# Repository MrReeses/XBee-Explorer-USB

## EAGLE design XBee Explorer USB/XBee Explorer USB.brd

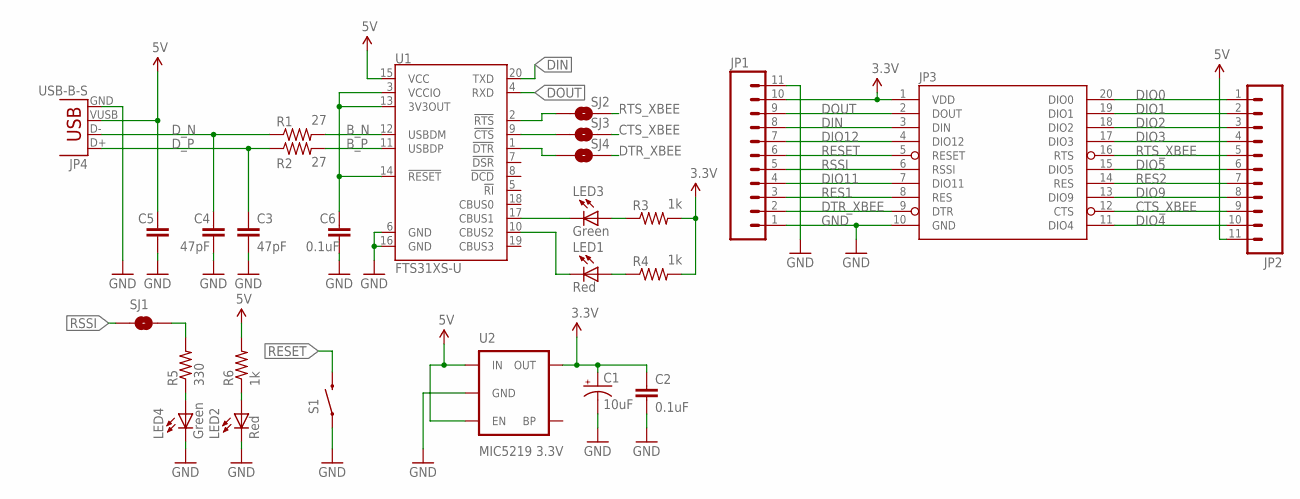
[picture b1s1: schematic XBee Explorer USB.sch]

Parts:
C1: 10uF; EIA3216
C2, C6: 0.1uF; 0805
C3, C4: 47pF; 0805
C5: CAP0805; 0805
JP1, JP2: M111X11_NO_SILK; 1X11_NO_SILK
JP3: XBEE-1B3; XBEE-SMD
JP4: USB-B-S; USB-B-SMT
LED1, LED2: Red; CHIP-LED0805
LED3, LED4: Green; CHIP-LED0805
R1, R2: 27; R0805
R3, R4, R6: 1k; R0805
R5: 330; R0805
S1: SWITCH-MOMENTARY-2SMD; TACTILE-SWITCH-SMD
SJ1, SJ2, SJ3, SJ4: SOLDERJUMPERTRACE; SJ_2S-TRACE
U1: FTS31XS-U; SSOP20_L
U2: MIC5219 3.3V; SOT23-5

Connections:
3.3V: C1.A (+), C2.1, JP1.10, JP3.1 (VDD), R3.2, R4.2, U2.5 (OUT)
5V: C5.1, JP2.11, JP4.VUSB (VBUS), R6.2, U1.15 (VCC), U2.1 (IN), U2.3 (EN)
B_N: R1.2, U1.12 (USBDM)
B_P: R2.2, U1.11 (USBDP)
CTS_XBEE: JP2.9, JP3.12 (CTS), SJ3.2
DIN: JP1.8, JP3.3 (DIN), U1.20 (TXD)
DIO0: JP2.1, JP3.20 (DIO0)
DIO1: JP2.2, JP3.19 (DIO1)
DIO2: JP2.3, JP3.18 (DIO2)
DIO3: JP2.4, JP3.17 (DIO3)
DIO4: JP2.10, JP3.11 (DIO4)
DIO5: JP2.6, JP3.15 (DIO5)
DIO9: JP2.8, JP3.13 (DIO9)
DIO11: JP1.4, JP3.7 (DIO11)
DIO12: JP1.7, JP3.4 (DIO12)
DOUT: JP1.9, JP3.2 (DOUT), U1.4 (RXD)
DTR_XBEE: JP1.2, JP3.9 (DTR), SJ4.2
D_N: C4.1, JP4.D-, R1.1
D_P: C3.1, JP4.D+, R2.1
GND: C1.C (-), C2.2, C3.2, C4.2, C5.2, C6.2, JP1.1, JP1.11, JP3.10 (GND), JP4.GND, LED2.C, LED4.C, S1.1, U1.6 (GND), U1.16 (GND), U2.2 (GND)
unnamed: SJ2.1, U1.2 (!RTS)
unnamed: SJ3.1, U1.9 (!CTS)
unnamed: SJ4.1, U1.1 (!DTR)
unnamed: R5.2, SJ1.2
unnamed: LED2.A, R6.1
unnamed: LED4.A, R5.1
unnamed: LED3.C, U1.17 (CBUS1)
unnamed: LED1.C, U1.10 (CBUS2)
unnamed: LED3.A, R3.1
unnamed: LED1.A, R4.1
unnamed: C6.1, U1.3 (VCCIO), U1.13 (3V3OUT), U1.14 (!RESET)
RES1: JP1.3, JP3.8 (RES)
RES2: JP2.7, JP3.14 (RES)
RESET: JP1.6, JP3.5 (RESET), S1.3 (2)
RSSI: JP1.5, JP3.6 (RSSI), SJ1.1
RTS_XBEE: JP2.5, JP3.16 (RTS), SJ2.2

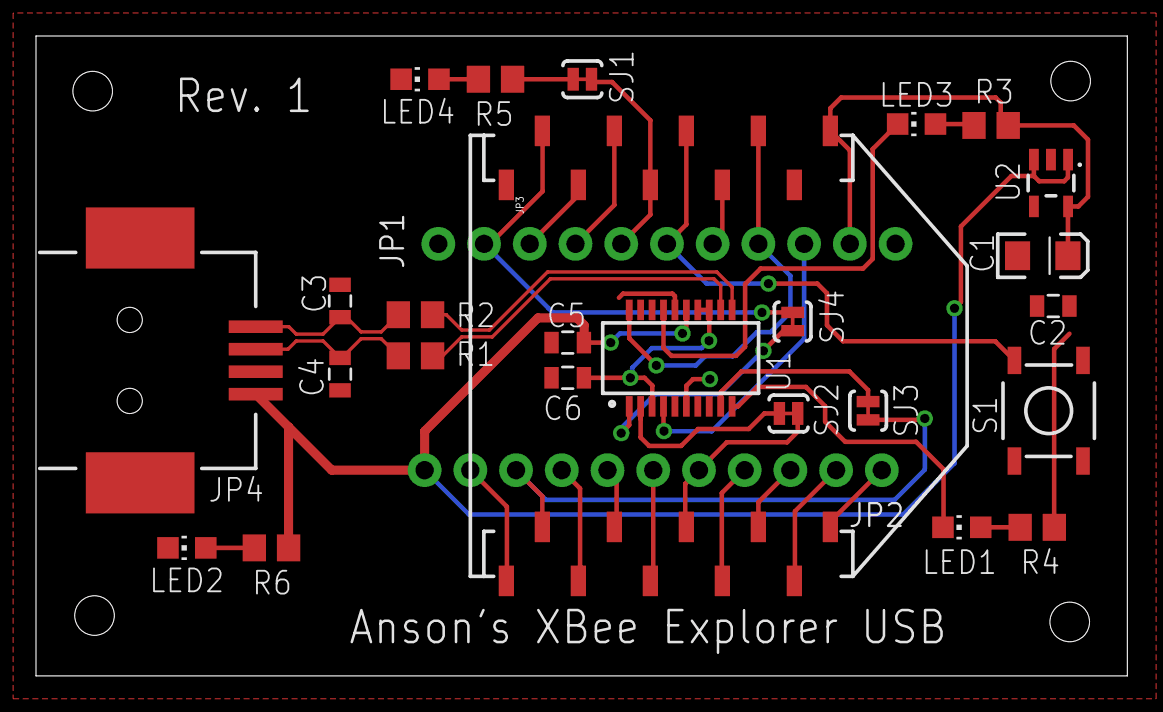
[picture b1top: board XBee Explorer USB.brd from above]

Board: 2 copper layers, 60.6 x 35.5 mm, 27 parts (0 on the bottom side), 36 nets.

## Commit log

2015-09-25 :circus_tent: Added .gitattributes & .gitignore files
2015-09-25 XBee Explorer USB
    These files are for the XBee Explorer USB board. It contains the
    schematic, board, and gerber files that were generated using Eagle.

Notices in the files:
parts and their libraries:
SparkFun-DigitalIC: Licensing: Creative Commons ShareAlike 4.0 International - https://creativecommons.org/licenses/by-sa/4.0
